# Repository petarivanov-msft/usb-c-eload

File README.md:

# USB-C-Eload-V1 — USB-C PD electronic load

Cheap DIY constant-current electronic load / bench tool. The USB-C port negotiates 5/9/12/15/20 V (USB PD sink) and a linear
MOSFET stage sinks an adjustable current (hardware-capped at about 1.09 A) from the negotiated rail. An STM32 handles the UI
(OLED + rotary encoder), measurement and PD voltage selection. The current loop and the safety cut-offs are analogue hardware,
independent of the firmware.

A KiCad 10 hardware design with STM32 firmware. Target: 5/9/12/15/20 V input, 0 to about 1 A constant current,
10 W passive or 20 W with a fan, 128×64 OLED, rotary encoder, hardware over-current and over-temperature cut-offs.
It was designed to be hand-assembled with paste and hot air (0603/0805, SOIC, TSSOP, ESSOP-EP, USB-C), as SMD practice and as a useful bench tool.

> **Status: designed and checked on paper, not built.** The schematic, PCB, fab files and firmware are complete.
> ERC: 0 violations. DRC: 0 violations, 0 unconnected, 0 schematic-parity issues (see `output/erc.json`, `output/drc_report.json`).
> The firmware compiles (24 KB of 32 KB flash) but has **never run on hardware**. No board has been ordered or powered yet.
> Expect to debug it, and read the open items below before ordering.
>
> **Safety:** this is a hobby design with no warranty. It dissipates up to 20 W in a MOSFET with a live drain tab (at VBUS),
> and the VBUS output terminal is not current-limited. The author is not responsible for damaged sources, boards or fingers.
>
> **Licences:** hardware (schematic, PCB, BOM, docs) CERN-OHL-P-2.0 (`LICENSE-HARDWARE.txt`). Firmware MIT (`firmware/LICENSE`).

## Sourcing notes (checked 16 Nov 2026)

- **Q1 (FQP30N06L) is discontinued.** onsemi marked it end-of-life, LCSC lists it as discontinued, and Mouser UK doesn't sell it.
  It was chosen because its datasheet has a published DC SOA line, which linear-mode operation needs. Options:
  - small eBay or broker lots of "FQP30N06L" (unverified origin, so treat as untrusted until tested), or
  - the Infineon IRLZ44N (LCSC C38774), which has the same TO-220 G-D-S pinout, runs from a 5 V gate and is readily available,
    but has a pulse-only SOA graph. Start at the 10 W limit if you use it.
  - The "FQP30N06L-VB" listed on LCSC (C878826) uses a recycled Vishay IRL540 datasheet with no DC SOA line, so it is not recommended for linear mode.
- **L1 (Sunlord SWPA4030S4R7MT, C57269)** isn't available through LCSC's international site. The substitute I picked for the cart is the APV
  ANR4018T4R7M (C7427102, 4×4 mm, 4.7 µH, 2.2 A saturation). Check its recommended land pattern against the KiCad
  `L_Sunlord_SWPA4030S` footprint before soldering.
- LCSC ships with minimum quantities (50 or 100 for 0603 parts), so a full set costs about $30 for parts plus shipping, and the PCBs are about $4 plus shipping for five.
  `output/LCSC_order_2boards.csv` is a ready-to-upload BOM (two boards plus spares, with the L1 substitution).

*KiCad 3D render of the board. The USB-C receptacle (left edge) and rotary encoder (top right) are simplified placeholder blocks, because KiCad's library has no 3D models for those parts (3d/). The OLED module isn't modelled. In the finished tool the OLED plugs into J2, and the TO-220 MOSFET (top-left) sits on a heatsink that hangs over the board edge.*

## Files

| Path | What |
|---|---|
| `USB-C-Eload-V1.kicad_sch` | Schematic (single A2 sheet, label-connected, 102 parts) |
| `USB-C-Eload-V1.kicad_pcb` | **100 x 75 mm, 2-layer, routed** board |
| `USB-C-Eload-V1.kicad_pro` | Project, net classes and DRC rules |
| `eload.kicad_sym`, `sym-lib-table` | Project symbol library (CH224A) |
| `output/USB-C-Eload-V1_gerbers.zip` | Gerbers + drill files for JLCPCB (the same files are in `output/gerbers/`) |
| `output/BOM_V1.csv` | BOM with LCSC and MPN (grouped), as drawn in the schematic |
| `output/LCSC_order_2boards.csv` | LCSC BOM-tool upload: two boards plus spares, with the L1 substitute |
| `output/CPL_V1.csv` | Pick-and-place (top side only), origin = bottom-left corner of the board, Y up |
| `output/firmware/` | Compiled `.bin` / `.hex` / `.elf` (flash at 0x08000000 with an ST-Link) |
| `output/schematic.pdf`, `layout_top.png`, `layout_bottom.png` | Review documents |
| `firmware/` | PlatformIO project (`python -m platformio run`, `... -t upload` with an ST-Link on J3) |
| `hardware-tools/` | Python generators: `gen_eload.py` (schematic), `layout/` (PCB, a record of how the board was produced; paths inside are examples such as `C:\work\eload` and need adjusting, and routing needs Freerouting with Java 25) |

## Ordering from JLCPCB

- Upload `output/USB-C-Eload-V1_gerbers.zip`. Choose 2 layers, 100 x 75 mm, 1.6 mm, any colour, HASL (lead-free is easier for hand soldering).
- Minimum track/space is 0.15 mm and the smallest via is 0.5/0.3 mm (JLC's standard tier), so no "advanced" options are needed.
- **Do not select assembly** (you are soldering it yourself). If you want a stencil, order the `F_Paste` layer from the same Gerbers.
- `CPL_V1.csv` is provided in case you change your mind (all parts are on the top side).
  Check the rotations of the TSSOP/ESSOP/USB-C parts on JLC's preview before accepting.
- Buy the parts from `BOM_V1.csv` (or upload `output/LCSC_order_2boards.csv` to the LCSC BOM tool). **Q1 and L1 need substitutes, see "Sourcing notes" above.** Do not swap in a different MOSFET without checking its DC SOA (see below).
- Parts without an LCSC code: SW2/SW3 (any 6 x 6 mm 4-pin through-hole tact switch, 5 mm high), test points (bare pads, nothing to buy), mounting holes.

## Verified design decisions

| Area | Decision | Evidence |
|---|---|---|
| PD controller | **CH224A** (ESSOP-10-EP), I²C mode, Rset 6.8 k = 9 V power-up default | CH224K has no I²C, and its I/O-level table has no 15 V on CH224A. CH224A is pin-compatible with K and supports 5/9/12/15/20/28 V via I²C register 0x0A (addr 0x22/0x23). VHV tolerates 32 V. |
| Load MOSFET | **FQP30N06L** TO-220 | Only candidate with a *published DC SOA line* (about 3.9 A at 20 V, Tc = 25 °C). IRLZ44N / IRL540N SOA graphs show single pulses only. Logic-level, RthJC 1.9 °C/W, tab = drain = VBUS. |
| Rails | AP63205 buck → **5 V** → AP2112K LDO → **3.3 V** | 5 V op-amp rail gives at least 3.9 V gate drive (about 2.9 V needed worst case at 1 A). LDO gives a quiet ADC reference. TLV9062 abs max supply is 6 V. |
| Current sense | 0.33 Ω 1 % 2512 shunt, 330 mV at 1 A | Offset error ≤ ±5 mA; ADC 2.4 mA/LSB raw. |
| Setpoint | PWM (TIM14, 12-bit, 15.6 kHz) → /9.2 divider → 2nd-order RC (about 16 Hz) | 0.27 mA/step; passive hardware cap **1.09 A** nominal (worst about 1.14 A). |
| Loop | TLV9062 integrator (Rin 10 k, Cf 10 nF), 3 mV idle bias so it rails low (no wind-up) | Outer-loop crossover 50–800 Hz; above 1.6 kHz it is a unity follower (datasheet PM 55°). **Check with a load step at bring-up.** |

### Operating envelope (thermal reality)

Q1 dissipates V × I: **20 W at 20 V / 1 A**. TO-220 stack: Tj = Ta + P × (1.9 + RthCS + RthSA).

| Cooling | Safe continuous power |
|---|---|
| Heatsink about 6 °C/W + insulating pad | about 5–8 W |
| Heatsink about 3 °C/W + insulating pad, still air | about 10 W (Tj about 90 °C) |
| 3 °C/W heatsink + 5 V fan (J6), about 1.5 °C/W effective | **20 W** (Tj about 125 °C) |

20 W is therefore a *fan-cooled* rating. The firmware defaults to a 10 W limit and only allows 20 W after you select "fan fitted"
(long-press the PD button). Q1's tab is at VBUS: use a silicone pad and a shoulder washer if the heatsink can touch anything.
Q1 sits at the top-left, tab facing the top edge, so the heatsink can hang over the edge. Mount the 10 k NTC on the heatsink/tab.

### Protection architecture (independent of firmware)

KILL bus (active high) = OR of 4 sources via 2× BAT54C, clamping **GATE** (Q3, BSS138) and **VSET** (Q2, BSS138):

1. `LOAD_DIS`, pulled up to 3V3 by 10 k, so an MCU reset or hang means load off. The MCU drives it low to enable.
2. Over-temperature comparator (U3B): trips at about 98 °C, releases at about 84 °C (NTC on J4).
3. NTC open / very cold detect (U6A): trips if the NTC voltage is above 3.0 V, so an **unplugged NTC kills the load**.
4. Overcurrent comparator (U6B): trips at about 1.38 A (range 1.28–1.47 A) on the shunt, independent of the loop.

`HW_FAULT` (PA3) reports the KILL bus to the MCU. Input path order: USB-C → **F1 2 A fuse** → TVS (SMAJ20A, 32.4 V clamp), CH224A, buck, load.
Not protected: the CH224A abs max (32 V) is slightly below the TVS clamp at full surge current. Acceptable for a hobby tool,
but do not hot-plug it onto abusive sources. The VBUS output terminal (J5) is **not** current-limited; do not use it as a power injector.

## PCB notes

- 2 layers: signal routing on both, solid GND pours on both sides stitched with vias, every GND pad has its own via.
  Current routing was by Freerouting after a seeded simulated-annealing placement. Layout details are in `hardware-tools/layout/`.
- Net classes: Power (VBUS, SH_TOP) 0.8 mm tracks, Mid (5 V, 3V3, GATE, SW) 0.4 mm, everything else 0.2 mm.
- The shunt top node (SH_TOP) is tapped by R7 and the ADC filter. Measured trace resistance between the tap and the shunt pad is
  below 3 mΩ (under 1 % current error at worst), and the boot-time offset calibration removes the rest.
- J1 USB-C at the left edge, J5 screw terminal at the bottom, J3 SWD bottom-right, J2 OLED header, encoder and the two buttons on the right.
- 4× M3 holes at the corners. Use standoffs: the TO-220 heatsink, NTC lead and fan lead are all at the top-left of the board.
- CH224A has an exposed pad (pin 11, GND). The KiCad EP size (2.1 × 3.3 mm) is a library estimate, WCH does not publish it.
  Measure the real part before ordering a stencil.
- Silkscreen has some cosmetic overlaps (the title, a few labels); DRC silk checks are disabled for that reason. It does not affect function.

## MCU pin map (STM32G030F6P6, TSSOP-20)

| Pin | Net | Function |
|---|---|---|
| 1 PB8 / 2 PB9 / 3 PC15 | BTN_LOAD / BTN_PD / ENC_SW | Inputs, internal pull-up, button to GND |
| 6 NRST / 18 PA13 / 19 PA14 | NRST / SWDIO / SWCLK | J3 (PA14 is also BOOT0, leave unpulled) |
| 7 PA0 / 8 PA1 / 9 PA2 | VBUS_SENSE / I_SENSE / NTC_SENSE | ADC1_IN0/1/2 |
| 10 PA3 | HW_FAULT | Input (3.13 V when a comparator is killing the load) |
| 11 PA4 | SET_PWM | TIM14_CH1 (AF4) |
| 12 PA5 | LOAD_DIS | Output, **low = load allowed** (hi-Z/high = off) |
| 13 PA6 / 14 PA7 | ENC_A / ENC_B | Encoder (EXTI interrupts in firmware) |
| 15 PA8 / 20 PB3 | LED_FAULT / LED_LOAD | Outputs |
| 16 PA11 / 17 PA12 | I2C_SCL / I2C_SDA | CH224A + OLED (bit-banged in firmware; PA11/PA12 are I2C2 at reset) |

## Firmware

Build: `cd firmware && python -m platformio run` (output `firmware/.pio/build/eload_g030/`). A prebuilt copy is in `output/firmware/`.
Upload with an ST-Link on J3: `python -m platformio run -t upload`. J3 pins: 1 GND, 2 SWCLK, 3 SWDIO, 4 NRST. There is **no 3V3 pin**,
so power the board from USB-C while programming (the ST-Link only needs GND, SWCLK, SWDIO and NRST; leave its 3V3 pin unconnected).
The OLED is driven with U8x8 text mode (small flash footprint); integer maths only.

Controls:

| Input | Action |
|---|---|
| Encoder turn | Set the load current (step size from the encoder button) |
| Encoder press | Toggle the current step between 10 mA and 50 mA |
| BTN_LOAD | Load on/off; also clears a latched fault |
| BTN_PD short press | Next PD voltage (5/9/12/15/20 V); the load is switched off first |
| BTN_PD long press | Toggle 10 W (passive) / 20 W ("fan fitted") power limit |

Safety behaviour: boots at 5 V with the load off; faults are latched (hardware trip, over-temperature 90 °C, NTC fault, VBUS
below 80 % of the request, power above 125 % of the limit, current above 1.25 A); current is derated from 70 °C. The independent
watchdog (1 s) resets the MCU if it hangs, which releases LOAD_DIS and switches the load off.

Calibration constants are at the top of `src/main.cpp` (shunt value, VBUS divider, ADC reference assumed 3300 mV, NTC table).
The zero-current offset is calibrated at boot with the load off.

## Assembly notes

- Hot-air/paste parts: CH224A (EP), STM32 TSSOP-20, TLV9062 ×2 (SOIC-8), AP63205 (TSOT-23-6), AP2112K, all the 0603/0805/1206 parts, USB-C (SMD signal pins plus 4 through-hole shell pins).
- Hand-solder: TO-220 (+ heatsink), encoder, buttons, pin headers, screw terminal.
- SSD1306 0.96" I²C modules come in two pin orders (GND-VCC-SCL-SDA vs VCC-GND-SCL-SDA). J2 is wired GND, 3V3, SCL, SDA. **Check your module before plugging it in.**
- NTC (10 k, B3950): bond it to the Q1 tab with thermal epoxy/Kapton, then plug it into J4. The load will not enable without it.

## Bring-up plan

1. Visual and continuity check, no Q1 fitted yet: with a 5 V source, 5 V rail about 5.0 V and 3V3 about 3.30 V.
2. Program via SWD; confirm the load stays off (TP_GATE about 0 V) while PA5 is hi-Z.
3. With a 9 V source: check `VSET` tracks the PWM, and that the Q1 gate rises, using a resistor load before fitting a heatsinked Q1.
4. Calibrate shunt/ADC, step the load 0 → 0.5 → 1 A at 5 V and check settling and no oscillation (TP_AMPOUT, TP_GATE).
5. Trip tests: unplug the NTC (load must drop), warm the NTC (trip at about 98 °C), force VSET high for the overcurrent test (about 1.38 A).
6. Thermal run: 10 W passive, then 20 W with the fan, watching the NTC and Q1 case temperature.

## Open items

- Check the real gate voltage at 1 A on the first board with a 5 V source (the 5 V rail may sag to about 4.5 V).
- Check the loop step response; adjust Cf (10 nF) if it rings.
- Confirm the CH224A exposed-pad size (stencil) and the OLED module pin order.
- Firmware is untested on hardware (pin and AF assumptions come from the ST open pin data); expect to tune calibration constants.
- Fan is always on when fitted. Consider a thermostat or thermal fuse as an extra independent cut-off.
- V2 ideas: current-limited power injection, constant-power/constant-resistance modes, Ah/Wh counting.

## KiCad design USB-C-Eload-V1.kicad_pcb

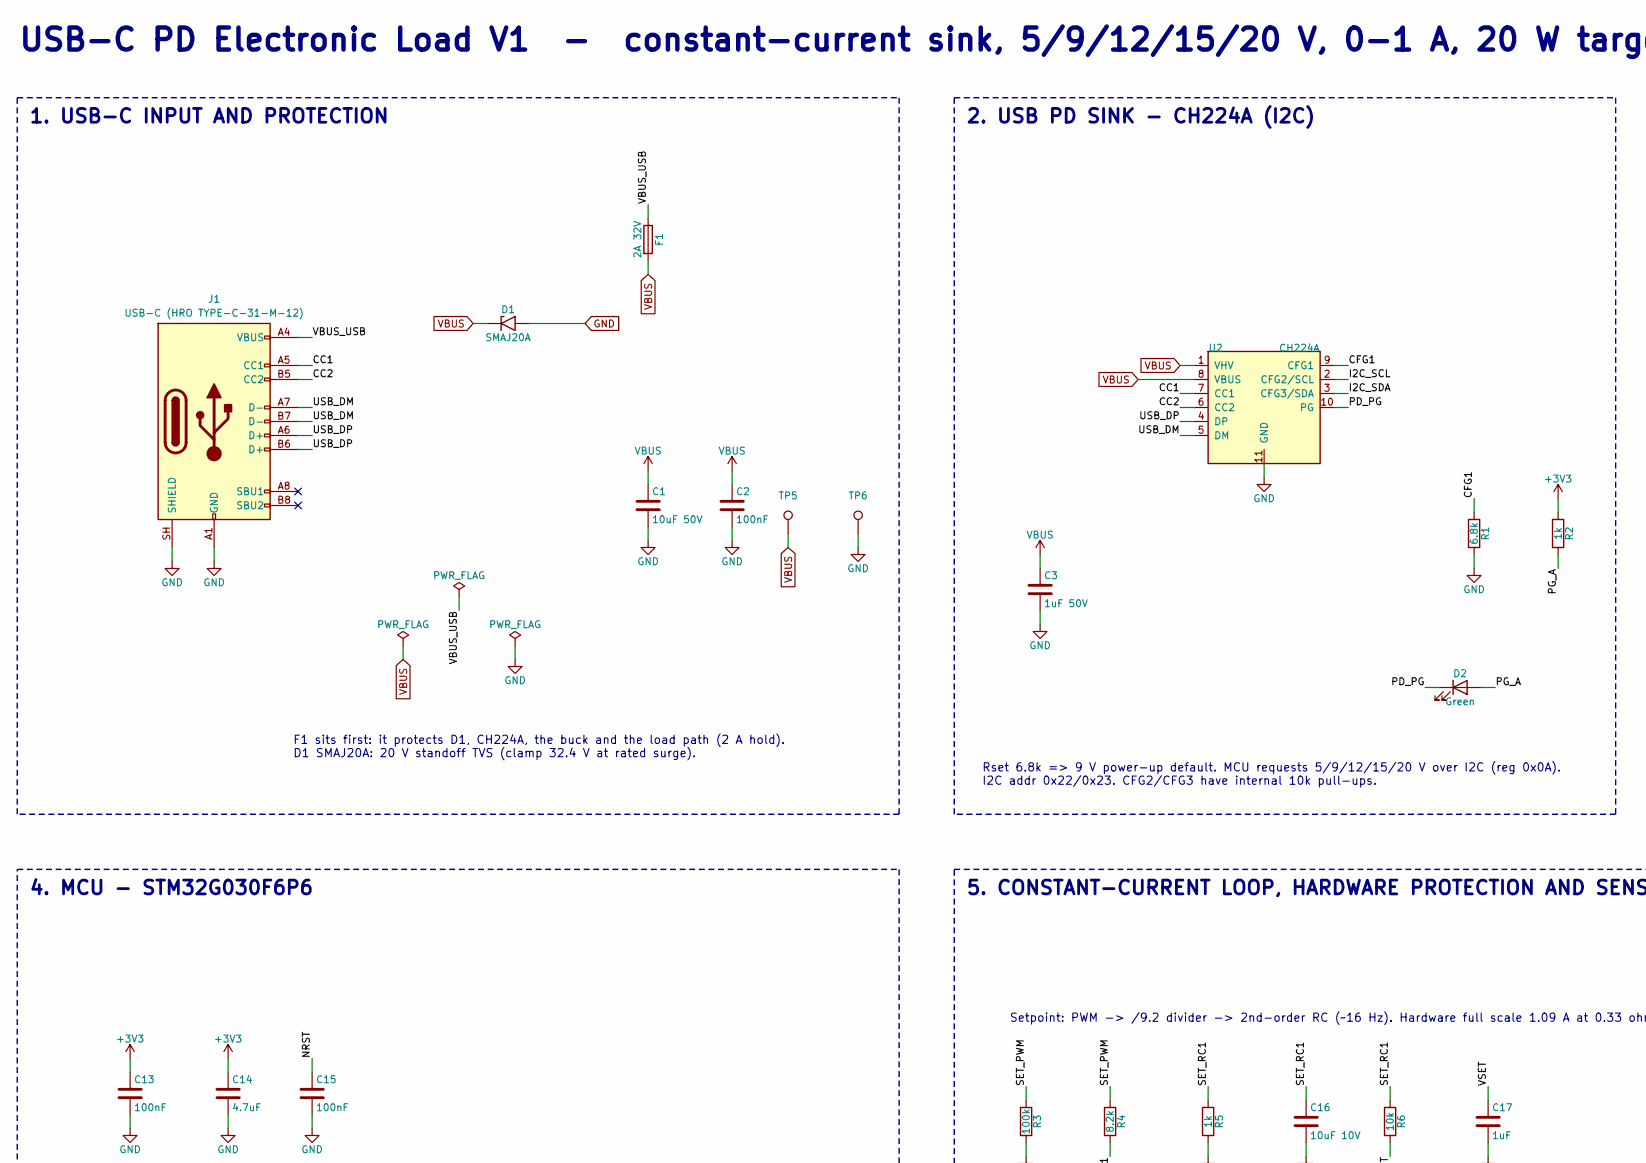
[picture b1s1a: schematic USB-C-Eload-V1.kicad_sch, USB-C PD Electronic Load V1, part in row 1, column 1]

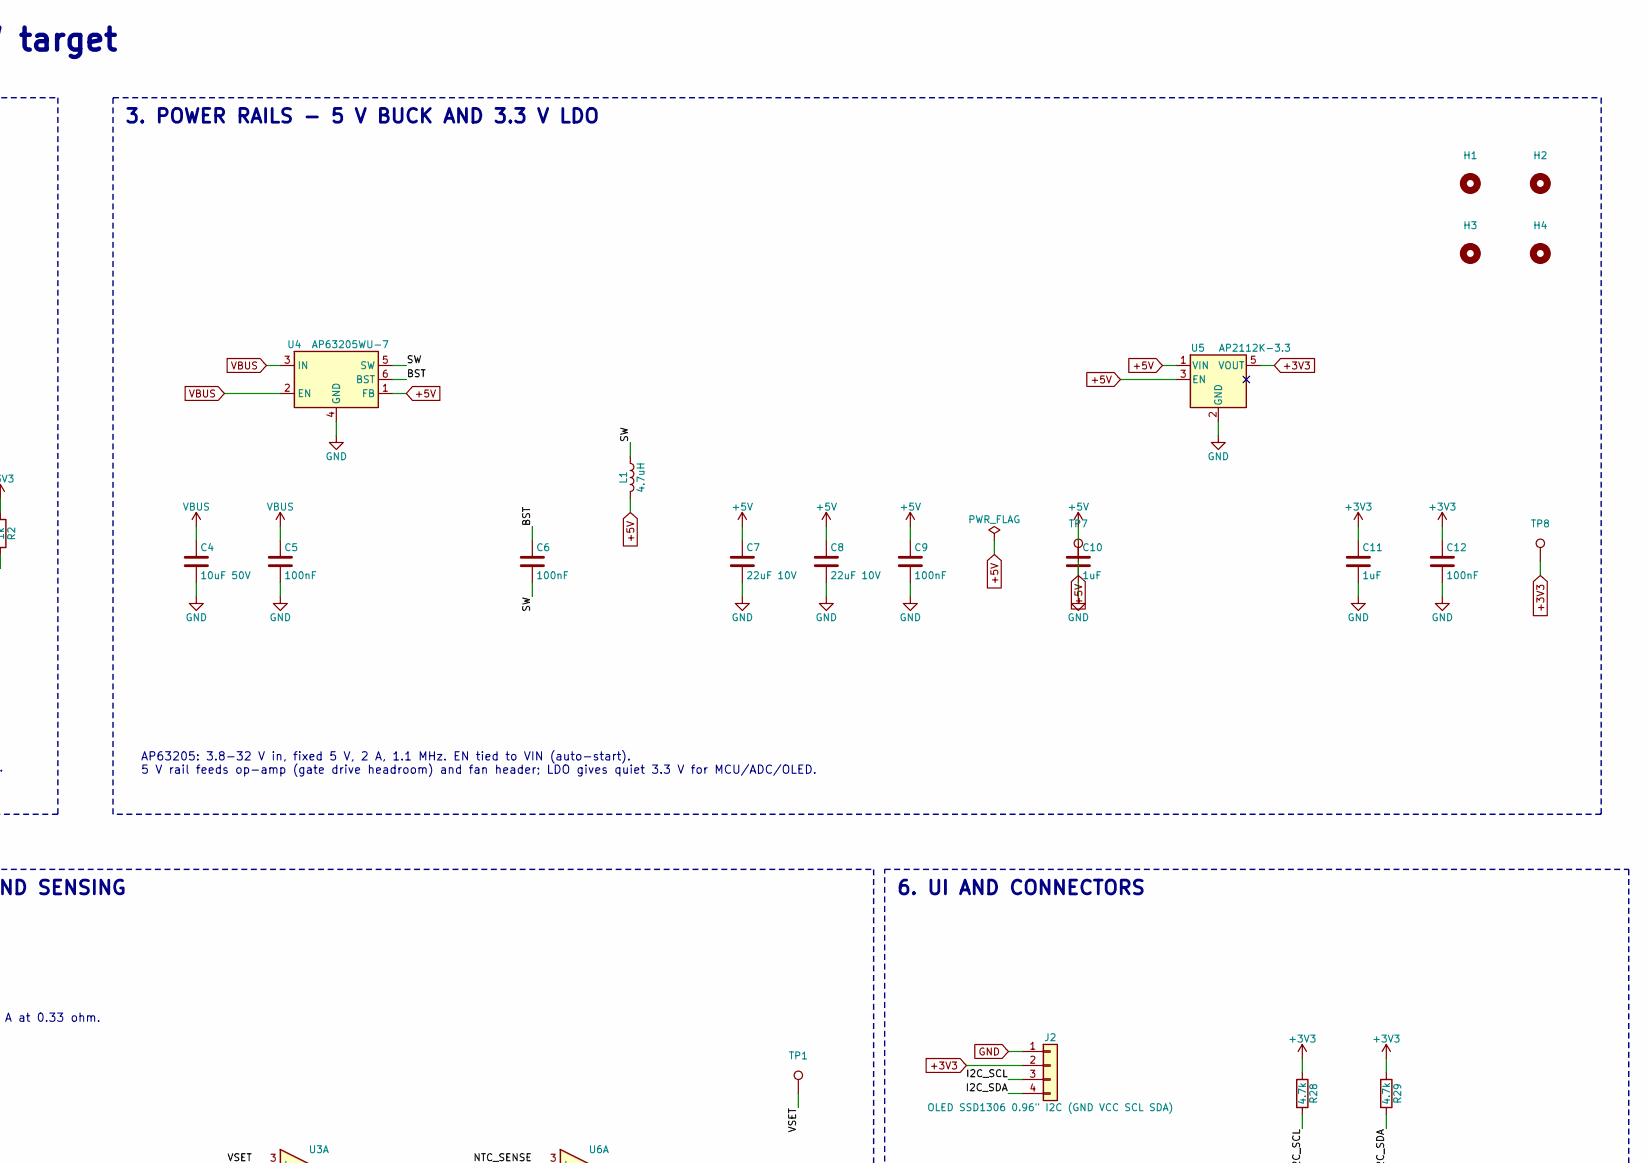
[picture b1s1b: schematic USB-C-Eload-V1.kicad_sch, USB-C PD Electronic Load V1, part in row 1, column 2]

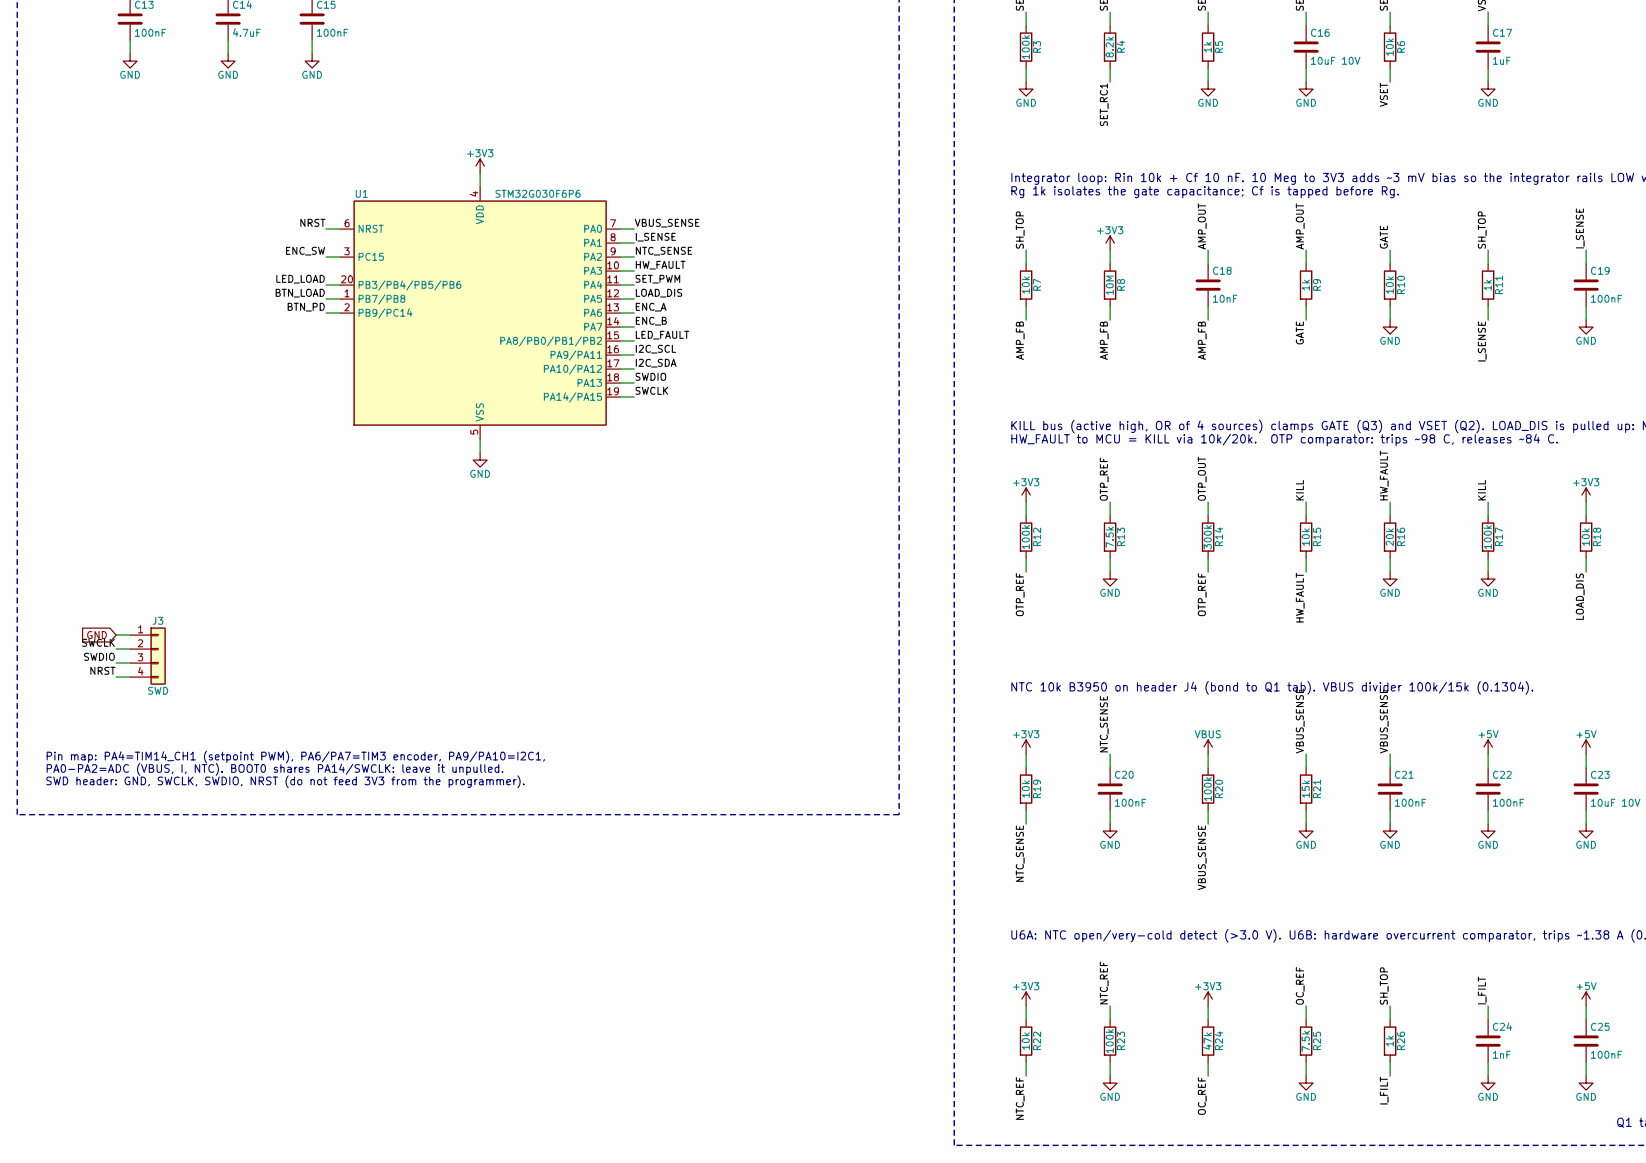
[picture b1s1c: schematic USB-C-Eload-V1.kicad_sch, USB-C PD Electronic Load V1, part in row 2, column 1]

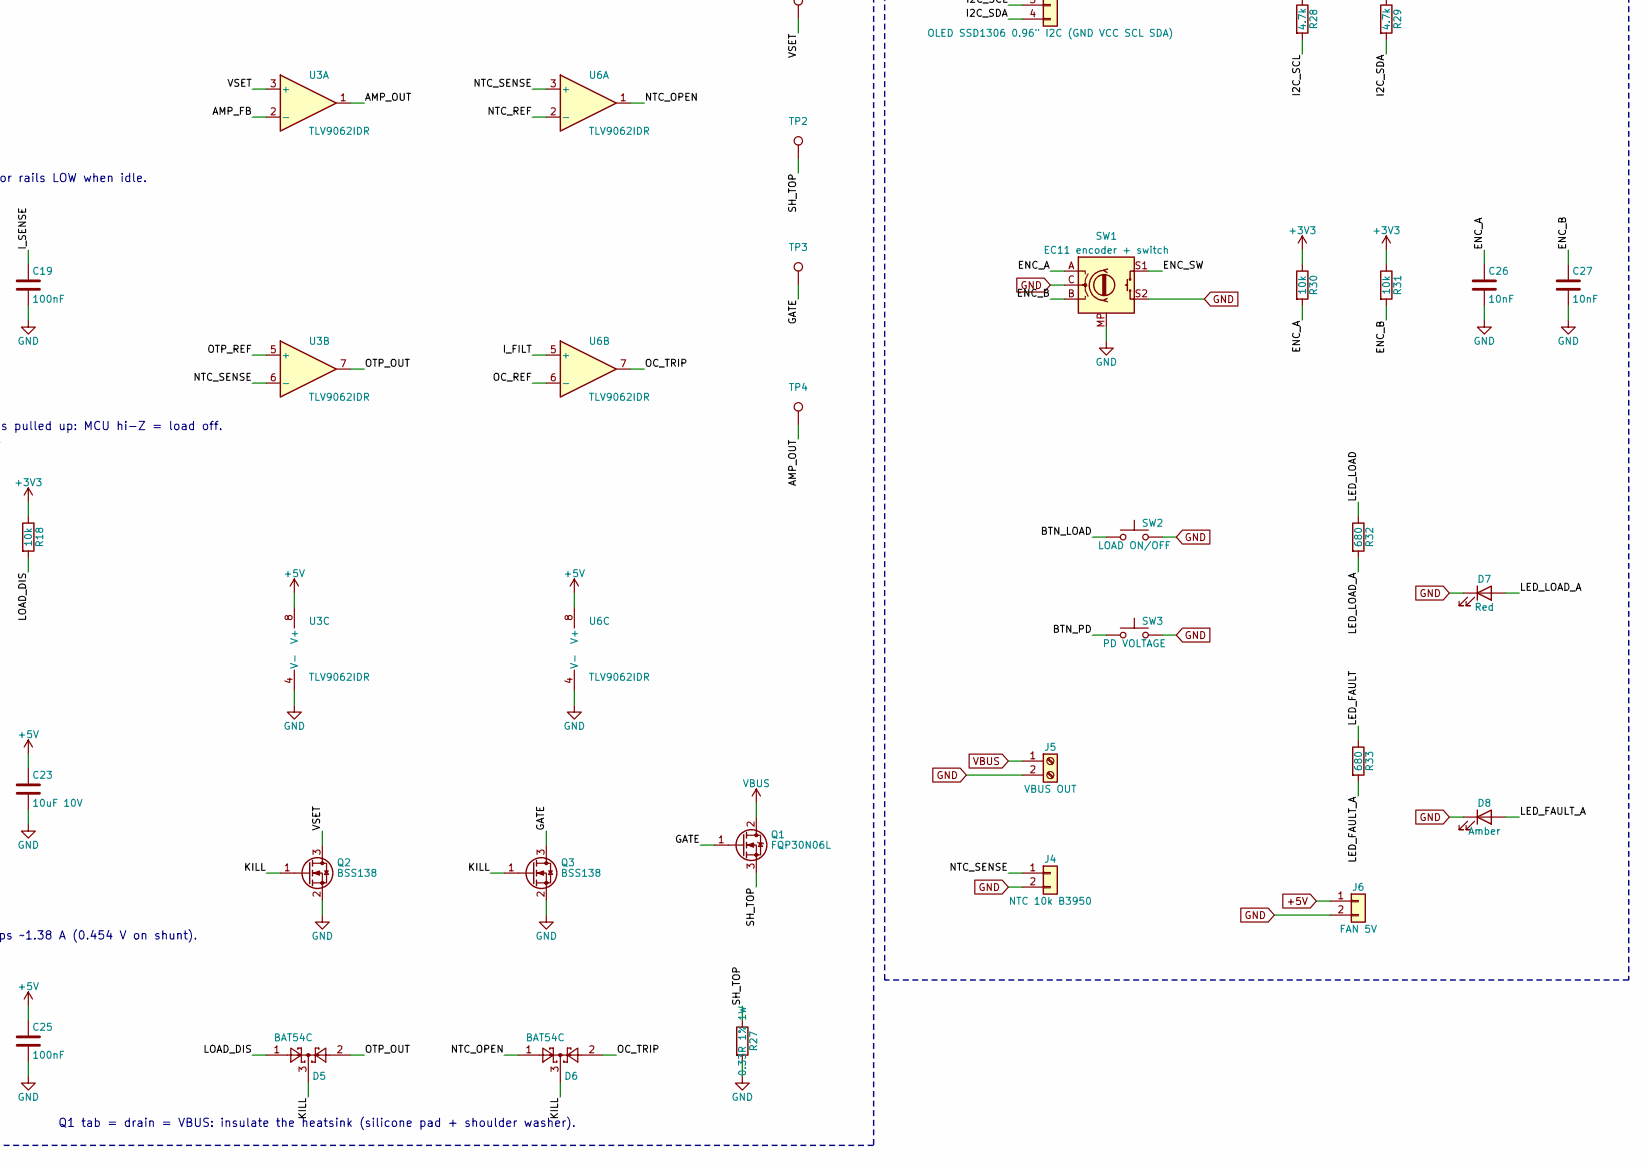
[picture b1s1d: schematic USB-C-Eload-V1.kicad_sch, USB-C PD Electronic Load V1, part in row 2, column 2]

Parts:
C1, C4: 10uF 50V; C_1206_3216Metric; MPN CL31A106KBHNNNE; LCSC C13585
C2, C5, C6, C9, C12, C13, C15, C19, C20, C21, C22, C25: 100nF; C_0603_1608Metric; MPN CL10B104KA8NNNC; LCSC C1590
C3: 1uF 50V; C_0805_2012Metric; MPN CL21B105KBFNNNE; LCSC C28323
C7, C8: 22uF 10V; C_0805_2012Metric; MPN CL21A226MPQNNNE; LCSC C29277
C10, C11, C17: 1uF; C_0603_1608Metric; MPN CL10B105KA8NNNC; LCSC C29936
C14: 4.7uF; C_0603_1608Metric; MPN CL10A475KP8NNNC; LCSC C1705
C16, C23: 10uF 10V; C_0603_1608Metric; MPN CL10A106KP8NNNC; LCSC C19702
C18, C26, C27: 10nF; C_0603_1608Metric; MPN CL10B103KB8NNNC; LCSC C1589
C24: 1nF; C_0603_1608Metric; MPN CL10B102KB8NNNC; LCSC C1588
D1: SMAJ20A; D_SMA; MPN SMAJ20A; LCSC C148209
D2: Green; LED_0603_1608Metric; MPN KT-0603G; LCSC C12624
D5, D6: BAT54C; SOT-23; MPN BAT54C,215; LCSC C37704
D7: Red; LED_0603_1608Metric; MPN KT-0603R; LCSC C2286
D8: Amber; LED_0603_1608Metric; MPN KT-0603Y; LCSC C2287
F1: 2A 32V; Fuse_1206_3216Metric; MPN 0440002.WR; LCSC C206969
H1, H2, H3, H4: M3; MountingHole_3.2mm_M3
J1: USB-C (HRO TYPE-C-31-M-12); USB_C_Receptacle_HRO_TYPE-C-31-M-12; MPN TYPE-C-31-M-12; LCSC C165948
J2: OLED SSD1306 0.96" I2C (GND VCC SCL SDA); PinHeader_1x04_P2.54mm_Vertical; MPN PZ254V-11-04P; LCSC C2691448
J3: SWD; PinHeader_1x04_P2.54mm_Vertical; MPN PZ254V-11-04P; LCSC C2691448
J4: NTC 10k B3950; PinHeader_1x02_P2.54mm_Vertical; MPN PZ254V-11-02P; LCSC C492401
J5: VBUS OUT; TerminalBlock_Phoenix_MKDS-1,5-2-5.08_1x02_P5.08mm_Horizont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; MPN KF128-5.08-2P; LCSC C474952
J6: FAN 5V; PinHeader_1x02_P2.54mm_Vertical; MPN PZ254V-11-02P; LCSC C492401
L1: 4.7uH; L_Sunlord_SWPA4030S; MPN SWPA4030S4R7MT; LCSC C57269
Q1: FQP30N06L; TO-220-3_Vertical; MPN FQP30N06L; LCSC C243087
Q2, Q3: BSS138; SOT-23; MPN BSS138; LCSC C52895
R1: 6.8k; R_0603_1608Metric; MPN 0603WAF6801T5E; LCSC C23212
R2, R5, R9, R11, R26: 1k; R_0603_1608Metric; MPN 0603WAF1001T5E; LCSC C21190
R3, R12, R17, R20, R23: 100k; R_0603_1608Metric; MPN 0603WAF1003T5E; LCSC C25803
R4: 8.2k; R_0603_1608Metric; MPN 0603WAF8201T5E; LCSC C25981
R6, R7, R10, R15, R18, R19, R22, R30, R31: 10k; R_0603_1608Metric; MPN 0603WAF1002T5E; LCSC C25804
R8: 10M; R_0603_1608Metric; MPN 0603WAF1005T5E; LCSC C7250
R13, R25: 7.5k; R_0603_1608Metric; MPN 0603WAF7501T5E; LCSC C23234
R14: 300k; R_0603_1608Metric; MPN 0603WAF3003T5E; LCSC C23024
R16: 20k; R_0603_1608Metric; MPN 0603WAF2002T5E; LCSC C4184
R21: 15k; R_0603_1608Metric; MPN 0603WAF1502T5E; LCSC C22809
R24: 47k; R_0603_1608Metric; MPN 0603WAF4702T5E; LCSC C25819
R27: 0.33R 1% 1W; R_2512_6332Metric; MPN RL2512FK-070R33L; LCSC C314696
R28, R29: 4.7k; R_0603_1608Metric; MPN 0603WAF4701T5E; LCSC C23162
R32, R33: 680; R_0603_1608Metric; MPN 0603WAF6800T5E; LCSC C23228
SW1: EC11 encoder + switch; RotaryEncoder_Alps_EC11E-Switch_Vertical_H20mm; MPN EC11E1834403; LCSC C361165
SW2: LOAD ON/OFF; SW_PUSH_6mm_H5mm
SW3: PD VOLTAGE; SW_PUSH_6mm_H5mm
TP1: TP_VSET; TestPoint_Pad_D1.5mm
TP2: TP_ISH; TestPoint_Pad_D1.5mm
TP3: TP_GATE; TestPoint_Pad_D1.5mm
TP4: TP_AMPOUT; TestPoint_Pad_D1.5mm
TP5: TP_VBUS; TestPoint_Pad_D1.5mm
TP6: TP_GND; TestPoint_Pad_D1.5mm
TP7: TP_5V; TestPoint_Pad_D1.5mm
TP8: TP_3V3; TestPoint_Pad_D1.5mm
U1: STM32G030F6P6; TSSOP-20_4.4x6.5mm_P0.65mm; MPN STM32G030F6P6TR; LCSC C529330
U2: CH224A; SSOP-10-1EP_3.9x4.9mm_P1mm_EP2.1x3.3mm; MPN CH224A; LCSC C42459160
U3, U6: TLV9062IDR; SOIC-8_3.9x4.9mm_P1.27mm; MPN TLV9062IDR; LCSC C398355
U4: AP63205WU-7; TSOT-23-6; MPN AP63205WU-7; LCSC C2071056
U5: AP2112K-3.3; SOT-23-5; MPN AP2112K-3.3TRG1; LCSC C51118

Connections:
+3V3: C11.1, C12.1, C13.1, C14.1, J2.2, R2.1, R8.1, R12.1, R18.1, R19.1, R22.1, R24.1, R28.1, R29.1, R30.1, R31.1, TP8.1, U1.4 (VDD), U5.5 (VOUT)
+5V: C7.1, C8.1, C9.1, C10.1, C22.1, C23.1, C25.1, J6.1, L1.2, TP7.1, U3.8 (V+), U4.1 (FB), U5.1 (VIN), U5.3 (EN), U6.8 (V+)
/AMP_FB: C18.2, R7.2, R8.2, U3.2 (-)
/AMP_OUT: C18.1, R9.1, TP4.1, U3.1
/BST: C6.1, U4.6 (BST)
/BTN_LOAD: SW2.1, U1.1 (PB7/PB8)
/BTN_PD: SW3.1, U1.2 (PB9/PC14)
/CC1: J1.A5 (CC1), U2.7 (CC1)
/CC2: J1.B5 (CC2), U2.6 (CC2)
/CFG1: R1.1, U2.9 (CFG1)
/ENC_A: C26.1, R30.2, SW1.A, U1.13 (PA6)
/ENC_B: C27.1, R31.2, SW1.B, U1.14 (PA7)
/ENC_SW: SW1.S1, U1.3 (PC15)
/GATE: Q1.1 (G), Q3.3 (D), R9.2, R10.1, TP3.1
/HW_FAULT: R15.2, R16.1, U1.10 (PA3)
/I2C_SCL: J2.3, R28.2, U1.16 (PA9/PA11), U2.2 (CFG2/SCL)
/I2C_SDA: J2.4, R29.2, U1.17 (PA10/PA12), U2.3 (CFG3/SDA)
/I_FILT: C24.1, R26.2, U6.5 (+)
/I_SENSE: C19.1, R11.2, U1.8 (PA1)
/KILL: D5.3, D6.3, Q2.1 (G), Q3.1 (G), R15.1, R17.1
/LED_FAULT: R33.1, U1.15 (PA8/PB0/PB1/PB2)
/LED_FAULT_A: D8.2 (A), R33.2
/LED_LOAD: R32.1, U1.20 (PB3/PB4/PB5/PB6)
/LED_LOAD_A: D7.2 (A), R32.2
/LOAD_DIS: D5.1, R18.2, U1.12 (PA5)
/NRST: C15.1, J3.4, U1.6 (NRST)
/NTC_OPEN: D6.1, U6.1
/NTC_REF: R22.2, R23.1, U6.2 (-)
/NTC_SENSE: C20.1, J4.1, R19.2, U1.9 (PA2), U3.6 (-), U6.3 (+)
/OC_REF: R24.2, R25.1, U6.6 (-)
/OC_TRIP: D6.2, U6.7
/OTP_OUT: D5.2, R14.1, U3.7
/OTP_REF: R12.2, R13.1, R14.2, U3.5 (+)
/PD_PG: D2.1 (K), U2.10 (PG)
/PG_A: D2.2 (A), R2.2
/SET_PWM: R3.1, R4.1, U1.11 (PA4)
/SET_RC1: C16.1, R4.2, R5.1, R6.1
/SH_TOP: Q1.3 (S), R7.1, R11.1, R26.1, R27.1, TP2.1
/SW: C6.2, L1.1, U4.5 (SW)
/SWCLK: J3.2, U1.19 (PA14/PA15)
/SWDIO: J3.3, U1.18 (PA13)
/USB_DM: J1.A7 (D-), J1.B7 (D-), U2.5 (DM)
/USB_DP: J1.A6 (D+), J1.B6 (D+), U2.4 (DP)
/VBUS_SENSE: C21.1, R20.2, R21.1, U1.7 (PA0)
/VBUS_USB: F1.1, J1.A4 (VBUS), J1.A9 (VBUS), J1.B4 (VBUS), J1.B9 (VBUS)
/VSET: C17.1, Q2.3 (D), R6.2, TP1.1, U3.3 (+)
GND: C1.2, C2.2, C3.2, C4.2, C5.2, C7.2, C8.2, C9.2, C10.2, C11.2, C12.2, C13.2, C14.2, C15.2, C16.2, C17.2, C19.2, C20.2, C21.2, C22.2, C23.2, C24.2, C25.2, C26.2, C27.2, D1.2 (A2), D7.1 (K), D8.1 (K), J1.A1 (GND), J1.A12 (GND), J1.B1 (GND), J1.B12 (GND), J1.SH (SHIELD), J2.1, J3.1, J4.2, J5.2, J6.2, Q2.2 (S), Q3.2 (S), R1.2, R3.2, R5.2, R10.2, R13.2, R16.2, R17.2, R21.2, R23.2, R25.2, R27.2, SW1.C, SW1.MP, SW1.S2, SW2.2, SW3.2, TP6.1, U1.5 (VSS), U2.11 (GND), U3.4 (V-), U4.4 (GND), U5.2 (GND), U6.4 (V-)
VBUS: C1.1, C2.1, C3.1, C4.1, C5.1, D1.1 (A1), F1.2, J5.1, Q1.2 (D), R20.1, TP5.1, U2.1 (VHV), U2.8 (VBUS), U4.2 (EN), U4.3 (IN)

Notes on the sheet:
USB-C PD Electronic Load V1 - constant-current sink, 5/9/12/15/20 V, 0-1 A, 20 W target
1. USB-C INPUT AND PROTECTION
F1 sits first: it protects D1, CH224A, the buck and the load path (2 A hold). D1 SMAJ20A: 20 V standoff TVS (clamp 32.4 V at rated surge).
2. USB PD SINK - CH224A (I2C)
Rset 6.8k => 9 V power-up default. MCU requests 5/9/12/15/20 V over I2C (reg 0x0A). I2C addr 0x22/0x23. CFG2/CFG3 have internal 10k pull-ups.
3. POWER RAILS - 5 V BUCK AND 3.3 V LDO
AP63205: 3.8-32 V in, fixed 5 V, 2 A, 1.1 MHz. EN tied to VIN (auto-start). 5 V rail feeds op-amp (gate drive headroom) and fan header; LDO gives quiet 3.3 V for MCU/ADC/OLED.
4. MCU - STM32G030F6P6
Pin map: PA4=TIM14_CH1 (setpoint PWM), PA6/PA7=TIM3 encoder, PA9/PA10=I2C1, PA0-PA2=ADC (VBUS, I, NTC). BOOT0 shares PA14/SWCLK: leave it unpulled. SWD header: GND, SWCLK, SWDIO, NRST (do not feed 3V3 from the programmer).
5. CONSTANT-CURRENT LOOP, HARDWARE PROTECTION AND SENSING
Setpoint: PWM -> /9.2 divider -> 2nd-order RC (~16 Hz). Hardware full scale 1.09 A at 0.33 ohm.
Integrator loop: Rin 10k + Cf 10 nF. 10 Meg to 3V3 adds ~3 mV bias so the integrator rails LOW when idle. Rg 1k isolates the gate capacitance; Cf is tapped before Rg.
KILL bus (active high, OR of 4 sources) clamps GATE (Q3) and VSET (Q2). LOAD_DIS is pulled up: MCU hi-Z = load off. HW_FAULT to MCU = KILL via 10k/20k. OTP comparator: trips ~98 C, releases ~84 C.
NTC 10k B3950 on header J4 (bond to Q1 tab). VBUS divider 100k/15k (0.1304).
U6A: NTC open/very-cold detect (>3.0 V). U6B: hardware overcurrent comparator, trips ~1.38 A (0.454 V on shunt).
Q1 tab = drain = VBUS: insulate the heatsink (silicone pad + shoulder washer).
6. UI AND CONNECTORS

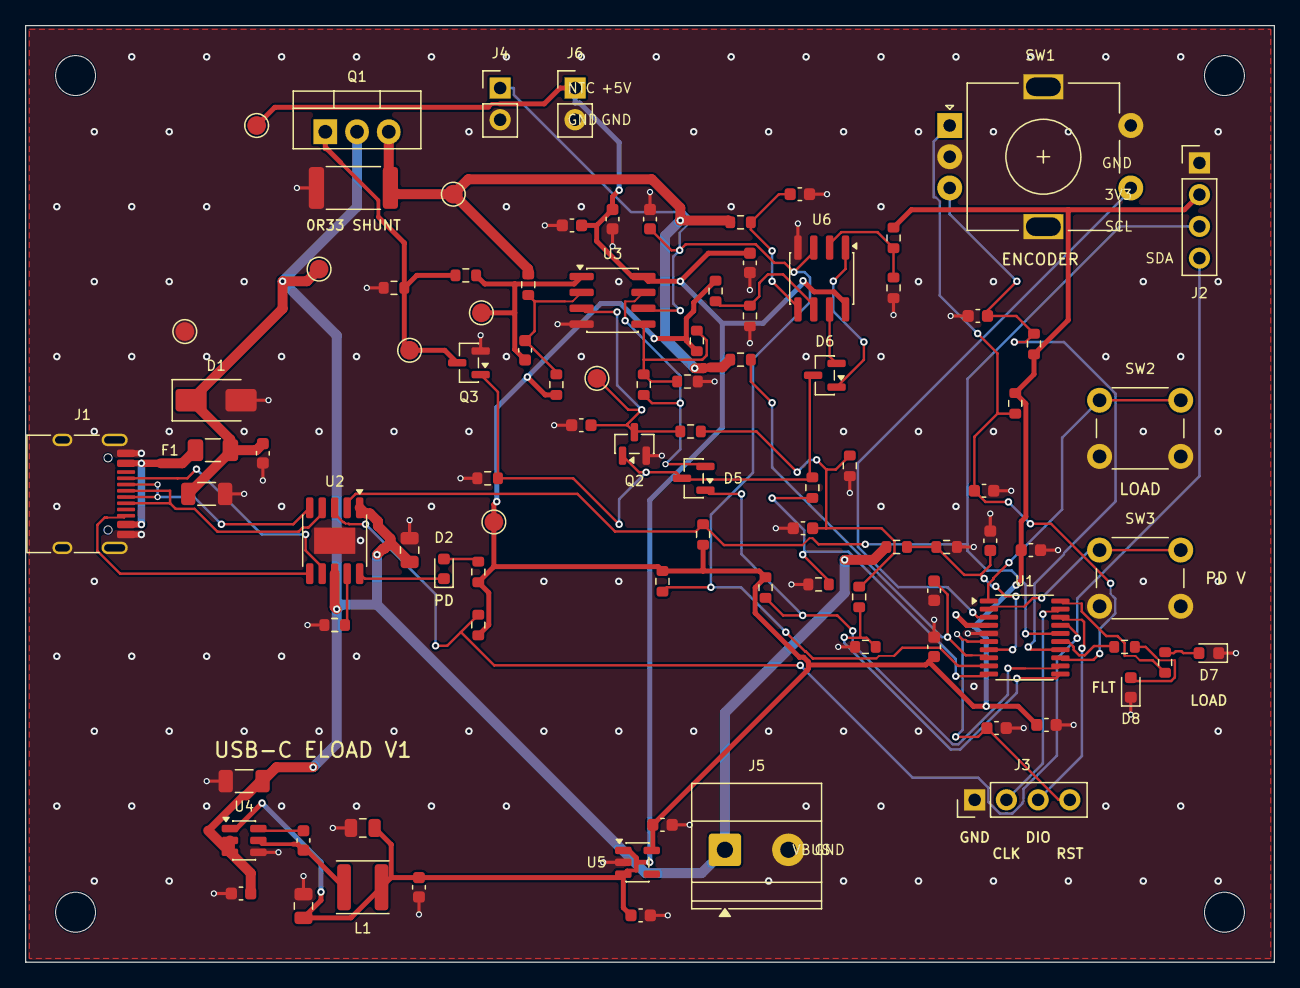
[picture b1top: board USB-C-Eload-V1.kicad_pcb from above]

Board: 2 copper layers, 100.0 x 75.0 mm, 98 parts (0 on the bottom side), 48 nets.

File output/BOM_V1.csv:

"Refs","Value","Footprint","Qty","LCSC","MPN"
"C1,C4","10uF 50V","Capacitor_SMD:C_1206_3216Metric","2","C13585","CL31A106KBHNNNE"
"C2,C5,C6,C9,C12,C13,C15,C19,C20,C21,C22,C25","100nF","Capacitor_SMD:C_0603_1608Metric","12","C1590","CL10B104KA8NNNC"
"C3","1uF 50V","Capacitor_SMD:C_0805_2012Metric","1","C28323","CL21B105KBFNNNE"
"C7,C8","22uF 10V","Capacitor_SMD:C_0805_2012Metric","2","C29277","CL21A226MPQNNNE"
"C10,C11,C17","1uF","Capacitor_SMD:C_0603_1608Metric","3","C29936","CL10B105KA8NNNC"
"C14","4.7uF","Capacitor_SMD:C_0603_1608Metric","1","C1705","CL10A475KP8NNNC"
"C16,C23","10uF 10V","Capacitor_SMD:C_0603_1608Metric","2","C19702","CL10A106KP8NNNC"
"C18,C26,C27","10nF","Capacitor_SMD:C_0603_1608Metric","3","C1589","CL10B103KB8NNNC"
"C24","1nF","Capacitor_SMD:C_0603_1608Metric","1","C1588","CL10B102KB8NNNC"
"D1","SMAJ20A","Diode_SMD:D_SMA","1","C148209","SMAJ20A"
"D2","Green","LED_SMD:LED_0603_1608Metric","1","C12624","KT-0603G"
"D5,D6","BAT54C","Package_TO_SOT_SMD:SOT-23","2","C37704","BAT54C,215"
"D7","Red","LED_SMD:LED_0603_1608Metric","1","C2286","KT-0603R"
"D8","Amber","LED_SMD:LED_0603_1608Metric","1","C2287","KT-0603Y"
"F1","2A 32V","Fuse:Fuse_1206_3216Metric","1","C206969","0440002.WR"
"H1,H2,H3,H4","M3","MountingHole:MountingHole_3.2mm_M3","4","",""
"J1","USB-C (HRO TYPE-C-31-M-12)","Connector_USB:USB_C_Receptacle_HRO_TYPE-C-31-M-12","1","C165948","TYPE-C-31-M-12"
"J2","OLED SSD1306 0.96"" I2C (GND VCC SCL SDA)","Connector_PinHeader_2.54mm:PinHeader_1x04_P2.54mm_Vertical","1","C2691448","PZ254V-11-04P"
"J3","SWD","Connector_PinHeader_2.54mm:PinHeader_1x04_P2.54mm_Vertical","1","C2691448","PZ254V-11-04P"
"J4","NTC 10k B3950","Connector_PinHeader_2.54mm:PinHeader_1x02_P2.54mm_Vertical","1","C492401","PZ254V-11-02P"
"J5","VBUS OUT","TerminalBlock_Phoenix:TerminalBlock_Phoenix_MKDS-1,5-2-5.08_1x02_P5.08mm_Horizontal","1","C474952","KF128-5.08-2P"
"J6","FAN 5V","Connector_PinHeader_2.54mm:PinHeader_1x02_P2.54mm_Vertical","1","C492401","PZ254V-11-02P"
"L1","4.7uH","Inductor_SMD:L_Sunlord_SWPA4030S","1","C57269","SWPA4030S4R7MT"
"Q1","FQP30N06L","Package_TO_SOT_THT:TO-220-3_Vertical","1","C243087","FQP30N06L"
"Q2,Q3","BSS138","Package_TO_SOT_SMD:SOT-23","2","C52895","BSS138"
"R1","6.8k","Resistor_SMD:R_0603_1608Metric","1","C23212","0603WAF6801T5E"
"R2,R5,R9,R11,R26","1k","Resistor_SMD:R_0603_1608Metric","5","C21190","0603WAF1001T5E"
"R3,R12,R17,R20,R23","100k","Resistor_SMD:R_0603_1608Metric","5","C25803","0603WAF1003T5E"
"R4","8.2k","Resistor_SMD:R_0603_1608Metric","1","C25981","0603WAF8201T5E"
"R6,R7,R10,R15,R18,R19,R22,R30,R31","10k","Resistor_SMD:R_0603_1608Metric","9","C25804","0603WAF1002T5E"
"R8","10M","Resistor_SMD:R_0603_1608Metric","1","C7250","0603WAF1005T5E"
"R13,R25","7.5k","Resistor_SMD:R_0603_1608Metric","2","C23234","0603WAF7501T5E"
"R14","300k","Resistor_SMD:R_0603_1608Metric","1","C23024","0603WAF3003T5E"
"R16","20k","Resistor_SMD:R_0603_1608Metric","1","C4184","0603WAF2002T5E"
"R21","15k","Resistor_SMD:R_0603_1608Metric","1","C22809","0603WAF1502T5E"
"R24","47k","Resistor_SMD:R_0603_1608Metric","1","C25819","0603WAF4702T5E"
"R27","0.33R 1% 1W","Resistor_SMD:R_2512_6332Metric","1","C314696","RL2512FK-070R33L"
"R28,R29","4.7k","Resistor_SMD:R_0603_1608Metric","2","C23162","0603WAF4701T5E"
"R32,R33","680","Resistor_SMD:R_0603_1608Metric","2","C23228","0603WAF6800T5E"
"SW1","EC11 encoder + switch","Rotary_Encoder:RotaryEncoder_Alps_EC11E-Switch_Vertical_H20mm","1","C361165","EC11E1834403"
"SW2","LOAD ON/OFF","Button_Switch_THT:SW_PUSH_6mm_H5mm","1","",""
"SW3","PD VOLTAGE","Button_Switch_THT:SW_PUSH_6mm_H5mm","1","",""
"TP1","TP_VSET","TestPoint:TestPoint_Pad_D1.5mm","1","",""
"TP2","TP_ISH","TestPoint:TestPoint_Pad_D1.5mm","1","",""
"TP3","TP_GATE","TestPoint:TestPoint_Pad_D1.5mm","1","",""
"TP4","TP_AMPOUT","TestPoint:TestPoint_Pad_D1.5mm","1","",""
"TP5","TP_VBUS","TestPoint:TestPoint_Pad_D1.5mm","1","",""
"TP6","TP_GND","TestPoint:TestPoint_Pad_D1.5mm","1","",""
"TP7","TP_5V","TestPoint:TestPoint_Pad_D1.5mm","1","",""
"TP8","TP_3V3","TestPoint:TestPoint_Pad_D1.5mm","1","",""
"U1","STM32G030F6P6","Package_SO:TSSOP-20_4.4x6.5mm_P0.65mm","1","C529330","STM32G030F6P6TR"
"U2","CH224A","Package_SO:SSOP-10-1EP_3.9x4.9mm_P1mm_EP2.1x3.3mm","1","C42459160","CH224A"
"U3,U6","TLV9062IDR","Package_SO:SOIC-8_3.9x4.9mm_P1.27mm","2","C398355","TLV9062IDR"
"U4","AP63205WU-7","Package_TO_SOT_SMD:TSOT-23-6","1","C2071056","AP63205WU-7"
"U5","AP2112K-3.3","Package_TO_SOT_SMD:SOT-23-5","1","C51118","AP2112K-3.3TRG1"

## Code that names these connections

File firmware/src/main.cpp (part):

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// The firmware sets the current target, picks the PD voltage, measures V/I/P/T and applies derating and protection.
//
// Safety rules implemented here:
//   * LOAD_DIS (PA5) is open-drain: released (hi-Z) = load off. It is only pulled low while the load is allowed.
//   * PWM setpoint is forced to 0 before every enable/disable and before every PD voltage change.
//   * Load never enables with a missing/shorted NTC, an active HW fault, or a VBUS that is not at the requested PD voltage.
//   * Independent watchdog (1 s). A hang releases LOAD_DIS via the reset.
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#include "stm32yyxx_ll_bus.h"

// ------------------------------------------------------------------ pins (see README pin map)
static const uint32_t PIN_VBUS_SENSE = PA0;
static const uint32_t PIN_I_SENSE    = PA1;
static const uint32_t PIN_NTC        = PA2;
static const uint32_t PIN_HW_FAULT   = PA3;
static const uint32_t PIN_SET_PWM    = PA4;   // TIM14_CH1
static const uint32_t PIN_LOAD_DIS   = PA5;   // low = load allowed, hi-Z = off
static const uint32_t PIN_ENC_A      = PA6;
static const uint32_t PIN_ENC_B      = PA7;
static const uint32_t PIN_LED_FAULT  = PA8;
static const uint32_t PIN_LED_LOAD   = PB3;
static const uint32_t PIN_BTN_LOAD   = PB8;
static const uint32_t PIN_BTN_PD     = PB9;
static const uint32_t PIN_ENC_SW     = PC15;

// ------------------------------------------------------------------ calibration constants
static const int32_t  VDDA_MV         = 3300;    // LDO output, adjust after measuring TP_3V3
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static const char* const FAULT_TXT[] = {"", "HW TRIP", "OVER TEMP", "NTC FAULT", "VBUS DROP", "OVER POWER", "OVER CURR"};

// ------------------------------------------------------------------ globals
static U8X8_SSD1306_128X64_NONAME_SW_I2C oled(PA11 /*SCL*/, PA12 /*SDA*/, U8X8_PIN_NONE);

static State  state = ST_OFF;
static Fault  fault = F_NONE;
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// ------------------------------------------------------------------ helpers
static void encIsr() {
  static const int8_t tbl[16] = {0, -1, 1, 0, 1, 0, 0, -1, -1, 0, 0, 1, 0, 1, -1, 0};
  encState = ((encState << 2) | (digitalRead(PIN_ENC_A) << 1) | digitalRead(PIN_ENC_B)) & 0x0F;
  encAccum += tbl[encState];
}

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static void loadRelease() {       // load off: PWM 0 first, then release LOAD_DIS
  setPwmFromMa(0);
  iCmd_mA = 0;
  digitalWrite(PIN_LOAD_DIS, HIGH);
  digitalWrite(PIN_LED_LOAD, LOW);
}

static void loadAllow() {
  setPwmFromMa(0);
  iCmd_mA = 0;
  digitalWrite(PIN_LOAD_DIS, LOW);
  digitalWrite(PIN_LED_LOAD, HIGH);
  enabledAt = millis();
}

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}

static void measure() {
  uint16_t av = adcAvg(PIN_VBUS_SENSE, 16);
  uint16_t ai = adcAvg(PIN_I_SENSE, 16);
  uint16_t an = adcAvg(PIN_NTC, 8);
  vbus_mV = ((int32_t)av * VDDA_MV / 4095) * VBUS_DIV_NUM / VBUS_DIV_DEN;
  int32_t vsh_uV = (int32_t)ai * UV_PER_COUNT_X16 / 16 - iOffset_uV;
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}

// ------------------------------------------------------------------ CH224A (bit-banged I2C on the OLED bus, open-drain emulation)
static const uint32_t I2C_SCL = PA11, I2C_SDA = PA12;
static inline void i2cDelay() { for (volatile uint8_t k = 0; k < 40; k++) { __NOP(); } }   // about 100 kHz at 64 MHz
static inline void sclLow()  { pinMode(I2C_SCL, OUTPUT); digitalWrite(I2C_SCL, LOW); }
static inline void sclHigh() { pinMode(I2C_SCL, INPUT_PULLUP); }
static inline void sdaLow()  { pinMode(I2C_SDA, OUTPUT); digitalWrite(I2C_SDA, LOW); }
static inline void sdaHigh() { pinMode(I2C_SDA, INPUT_PULLUP); }
static void i2cStart() { sdaHigh(); sclHigh(); i2cDelay(); sdaLow(); i2cDelay(); sclLow(); }
static void i2cStop()  { sdaLow(); i2cDelay(); sclHigh(); i2cDelay(); sdaHigh(); i2cDelay(); }
static bool i2cWrite(uint8_t d) {
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  if (!ntcOk) { tripFault(F_NTC); return; }
  if (temp_C >= T_FAULT_C) { tripFault(F_OVERTEMP); return; }
  if (now - enabledAt > 30) {
    if (digitalRead(PIN_HW_FAULT) == HIGH) {
      if (hwSince == 0) hwSince = now;
      if (now - hwSince > 30) { tripFault(F_HW); return; }
    } else hwSince = 0;
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
// ------------------------------------------------------------------ UI
struct Btn { uint32_t pin; bool last; uint32_t t; };
static Btn bLoad = {PIN_BTN_LOAD, true, 0}, bEnc = {PIN_ENC_SW, true, 0};
static uint32_t bPdDown = 0;

static bool pressed(Btn& b, uint32_t now) {      // falling edge with 30 ms debounce
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    else if (state == ST_FAULT) { if (ntcOk && temp_C < T_DERATE_START_C) { state = ST_OFF; fault = F_NONE; } }
    else if (canEnable()) { state = ST_ON; loadAllow(); hwSince = ocSince = vbusLowSince = 0; }
  }
  bool pdDown = !digitalRead(PIN_BTN_PD);
  if (pdDown && bPdDown == 0) bPdDown = now ? now : 1;
  if (!pdDown && bPdDown != 0) {
    uint32_t held = now - bPdDown; bPdDown = 0;
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
// ------------------------------------------------------------------ setup / loop
void setup() {
  pinMode(PIN_LOAD_DIS, OUTPUT_OPEN_DRAIN);
  digitalWrite(PIN_LOAD_DIS, HIGH);              // released: load off
  pinMode(PIN_LED_LOAD, OUTPUT); pinMode(PIN_LED_FAULT, OUTPUT);
  pinMode(PIN_HW_FAULT, INPUT);
  pinMode(PIN_BTN_LOAD, INPUT_PULLUP); pinMode(PIN_BTN_PD, INPUT_PULLUP); pinMode(PIN_ENC_SW, INPUT_PULLUP);
  pinMode(PIN_ENC_A, INPUT); pinMode(PIN_ENC_B, INPUT);

  // TIM14 CH1 on PA4 (AF4): 64 MHz / 4096 = 15.6 kHz, 12-bit PWM, driven straight from the LL driver
  LL_APB2_GRP1_EnableClock(LL_APB2_GRP1_PERIPH_TIM14);
  LL_GPIO_SetPinMode(GPIOA, LL_GPIO_PIN_4, LL_GPIO_MODE_ALTERNATE);
  LL_GPIO_SetAFPin_0_7(GPIOA, LL_GPIO_PIN_4, LL_GPIO_AF_4);
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
  delay(300);
  uint32_t acc = 0;                               // zero-current offset of the sense path
  for (uint8_t k = 0; k < 32; k++) { acc += analogRead(PIN_I_SENSE); IWatchdog.reload(); }
  iOffset_uV = (int32_t)(acc / 32) * UV_PER_COUNT_X16 / 16;
  if (iOffset_uV > IOFFSET_MAX_UV) iOffset_uV = IOFFSET_MAX_UV;

  attachInterrupt(digitalPinToInterrupt(PIN_ENC_A), encIsr, CHANGE);
  attachInterrupt(digitalPinToInterrupt(PIN_ENC_B), encIsr, CHANGE);
  pdProbe();
  pdApply(0);                                     // start at 5 V (CH224A powers up at 9 V from Rset)
  oled.clear();
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      else if (iCmd_mA > target) iCmd_mA = max(iCmd_mA - 50, target);
      setPwmFromMa(iCmd_mA);
    }
    digitalWrite(PIN_LED_FAULT, state == ST_FAULT ? ((now / 250) & 1) : (ntcOk ? LOW : HIGH));
  }
  if (now - tPd >= 500) { tPd = now; pdReadStatus(); }
  if (now - tUi >= 250) { tUi = now; drawUi(); }
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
